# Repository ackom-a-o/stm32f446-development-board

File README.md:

# STM32F446 Development Board

A custom, USB-powered development board for sensor and control experiments, built around the **STM32F446ZET6**. This project follows an embedded hardware design from component selection and PCB layout through assembly preparation, firmware and bench validation.

**Current milestone: prototype fabrication preparation.** The corrected design, fabrication exports and assembly data are published below. Hardware is not yet bench-tested; final assembler production-file approval and physical validation remain open.

*Composed from the current fabrication Gerbers. Top copper and silkscreen only; drill holes are not depicted. This is a design view, not an assembled-board photograph.*

[Schematic PDF](docs/schematic.pdf) · [Engineering review](docs/engineering-review.md) · [Validation evidence](docs/validation.md) · [Manufacturing package](manufacturing/prototype-r3/) · [First power-up](docs/bring-up.md)

## What the board provides

| Area | Implementation |
|---|---|
| MCU | STM32F446ZET6, Arm Cortex-M4, LQFP-144 |
| PCB | 80 × 70 mm, four copper layers, nominal 1.6 mm |
| Power | USB 5 V → protection → TPS7A2533 regulator → TPS22918 load switch → 3.3 V |
| Connectivity | USB 2.0 full-speed device, SPI, I²C, UART, analog and GPIO headers |
| CAN expansion | Classical CAN 2.0B on J7: PD0/RX and PD1/TX; requires an external 3.3 V logic-compatible transceiver |
| Debug | External SWD probe through a custom five-pin header |
| Clock | 8 MHz crystal |
| User controls | Three pushbuttons and three indicator LEDs |

USB host operation, USB Power Delivery and motor-power delivery are outside the current scope. The load switch controls rail startup; it is not a programmable current limiter.

```mermaid
flowchart LR
    USB[USB-C 5 V] --> Protection[Fuse and series diode]
    Protection --> LDO[TPS7A2533 regulator]
    LDO --> Switch[TPS22918 load switch]
    Switch --> Rail[3.3 V MCU and headers]
    Host[USB host data] <--> ESD[USBLC6 protection]
    ESD <--> MCU[STM32F446]
    Probe[External SWD probe] <--> MCU
    MCU <--> IO[SPI / I2C / UART / GPIO]
    MCU <--> CANHeader[J7: PD0 RX / PD1 TX]
    CANHeader <--> Transceiver[External CAN transceiver - required]
    Transceiver <--> CANBus[CANH / CANL bus]
```

CAN uses the MCU's existing CAN1 controller through J7 pin 3 (PD0/CAN1_RX) and pin 4 (PD1/CAN1_TX), configured as AF9. The transceiver and bus termination are external to this PCB. This is Classical CAN, not CAN FD, and firmware/link testing is pending.

## Engineering work behind the layout

The layout was reviewed against MCU and power-component datasheets, ST's USB hardware guidance and published signal-integrity advice. Checks covered electrical connectivity, local bypassing, ground return paths, USB geometry, reset/crystal placement, sourcing, footprint fit and assembly orientation. The [engineering review](docs/engineering-review.md) records the reasoning, corrections, references and remaining limits.

- **Reset routing:** moving C22 reduced its MCU reset route from **19.45 mm to 13.41 mm**, about 31%. The [before/after comparison](docs/design-decisions.md#reset-layout-iteration) records the improvement and remaining compromise.
- **Power margin:** a **250 mA total design budget** was screened against regulator dropout and dissipation. It remains conditional until load and thermal measurements establish the board's operating envelope.
- **Local bypassing:** C29 adds a dedicated 1 µF capacitor at the TPS22918 input instead of relying only on the regulator's more distant output capacitor.
- **Ground return:** a short PG9 inner-layer crossing was moved to the top layer to restore local ground beneath SWDIO. Ground stitching was retained; a geometric screen found no missing reference samples along the checked outer-layer routes.
- **Routing corners:** the remaining ordinary PF6 right-angle bend was replaced with chamfered routing. The saved-board audit found zero ordinary track-to-track 90° bends within its stated scope. [Why prefer 45° bends?](docs/engineering-review.md#routing-corners-why-prefer-45-degrees) They reduce abrupt geometry changes; a right angle alone does not prove a signal will fail.
- **Assembly data:** the supplier preview exposed header and chip rotation mismatches. Corrections were put into the placement file, uploaded and checked after a full quote reload.

Peer feedback and AI-assisted checks supported these iterations. Bench measurements will be reported separately from calculations and software checks.

## Evidence and next milestone

Recorded checks on **22 October 2026** report **0 ERC issues, 0 DRC violations, 0 unconnected items and 0 schematic parity issues**, with no ignored checks or current exclusions. The published inventory contains **66 assembly references**, plus three PCB test points. [Validation evidence](docs/validation.md) links the source hashes, reports and geometric checks; these do not establish measured hardware performance.

The fabricator has confirmed the nominal **JLC04161H-7628** construction used as the design basis. Next: approve final production files and bring up the prototype. The [bring-up checklist](docs/bring-up.md) starts with inspection, shorts and power rails, then SWD/reset, clock startup, GPIO and USB. Every physical test in the [test log](docs/test-log.md) remains **not tested**. Firmware will be added when implementation begins.

## Explore the design

Open [`stm32.kicad_pro`](stm32.kicad_pro) in **KiCad 10**, with its standard libraries installed.

The [four-sheet schematic](docs/schematic.pdf) separates power, USB/debug/clock, peripheral interfaces and expansion. The MCU uses eight symbol units so that supply pins and GPIO ports can be reviewed separately. Named signals connect sheets; pin numbers retain their physical package mapping.

*Sheet 3 of 4. The earlier readability refactor preserved its then-current 68 physical references and all 135 nets; [historical comparison evidence](docs/checks/schematic-refactor.json) records unchanged PCB geometry for that refactor. The subsequent C29 addition brings the current physical-reference count to 69.*

| Files | Purpose |
|---|---|
| `stm32.kicad_sch` | Root sheet: power path and MCU supplies |
| `usb_debug_clock.kicad_sch` | USB, clock, reset, boot and SWD |
| `mcu_interfaces.kicad_sch`, `gpio_expansion.kicad_sch` | MCU ports, peripheral headers and expansion |
| `stm32.kicad_pcb` | Routed four-layer PCB |
| `stm32.kicad_dru` | Project design rules |
| `STM32_Custom.pretty`, `STM32_Power.kicad_sym`, `STM32_MCU.kicad_sym` | Local footprints, power symbols and split MCU symbol |
| `fp-lib-table`, `sym-lib-table` | Project-relative library configuration |
| `docs/` | Schematic export, design decisions, part inventory and validation evidence |

Local libraries are included. The empty `Library.pretty` directory is retained for the existing project library table. The [prototype-r3 package](manufacturing/prototype-r3/) contains Gerbers/drills, BOM, supplier-adjusted placement data and file hashes. It is an unvalidated prototype package, not a production-qualified release. Placement rotations are supplier-specific; another assembler must check its own conventions.

## References and licensing

[STM32F446 datasheet](https://www.st.com/resource/en/datasheet/stm32f446ze.pdf) · [TPS7A25 datasheet](https://www.ti.com/lit/ds/symlink/tps7a25.pdf) · [TPS22918 datasheet](https://www.ti.com/lit/ds/symlink/tps22918.pdf)

A project hardware/documentation license has not yet been selected. No explicit open-source license is currently granted. Third-party assets remain subject to their respective licenses.

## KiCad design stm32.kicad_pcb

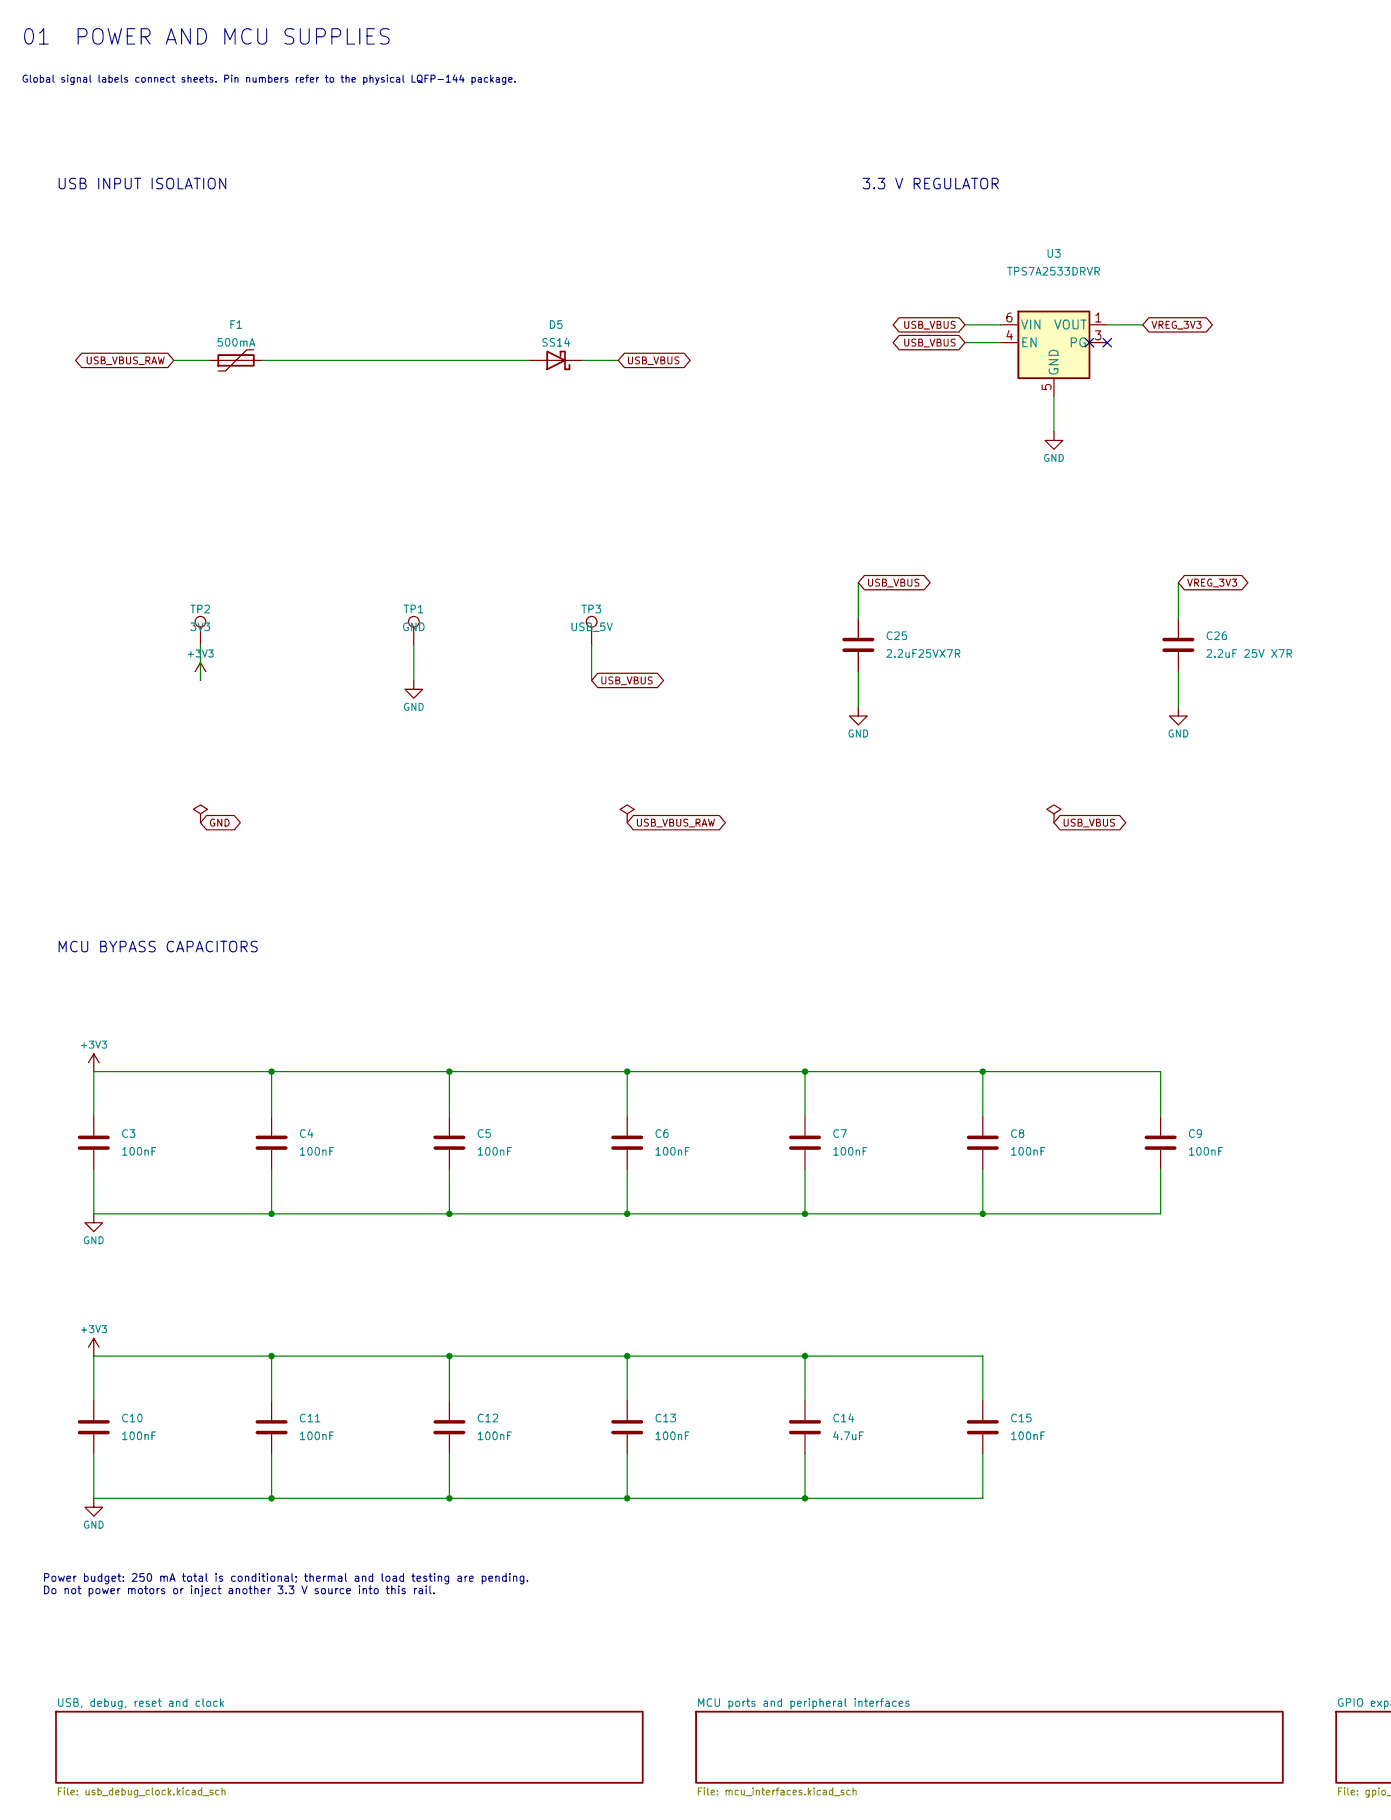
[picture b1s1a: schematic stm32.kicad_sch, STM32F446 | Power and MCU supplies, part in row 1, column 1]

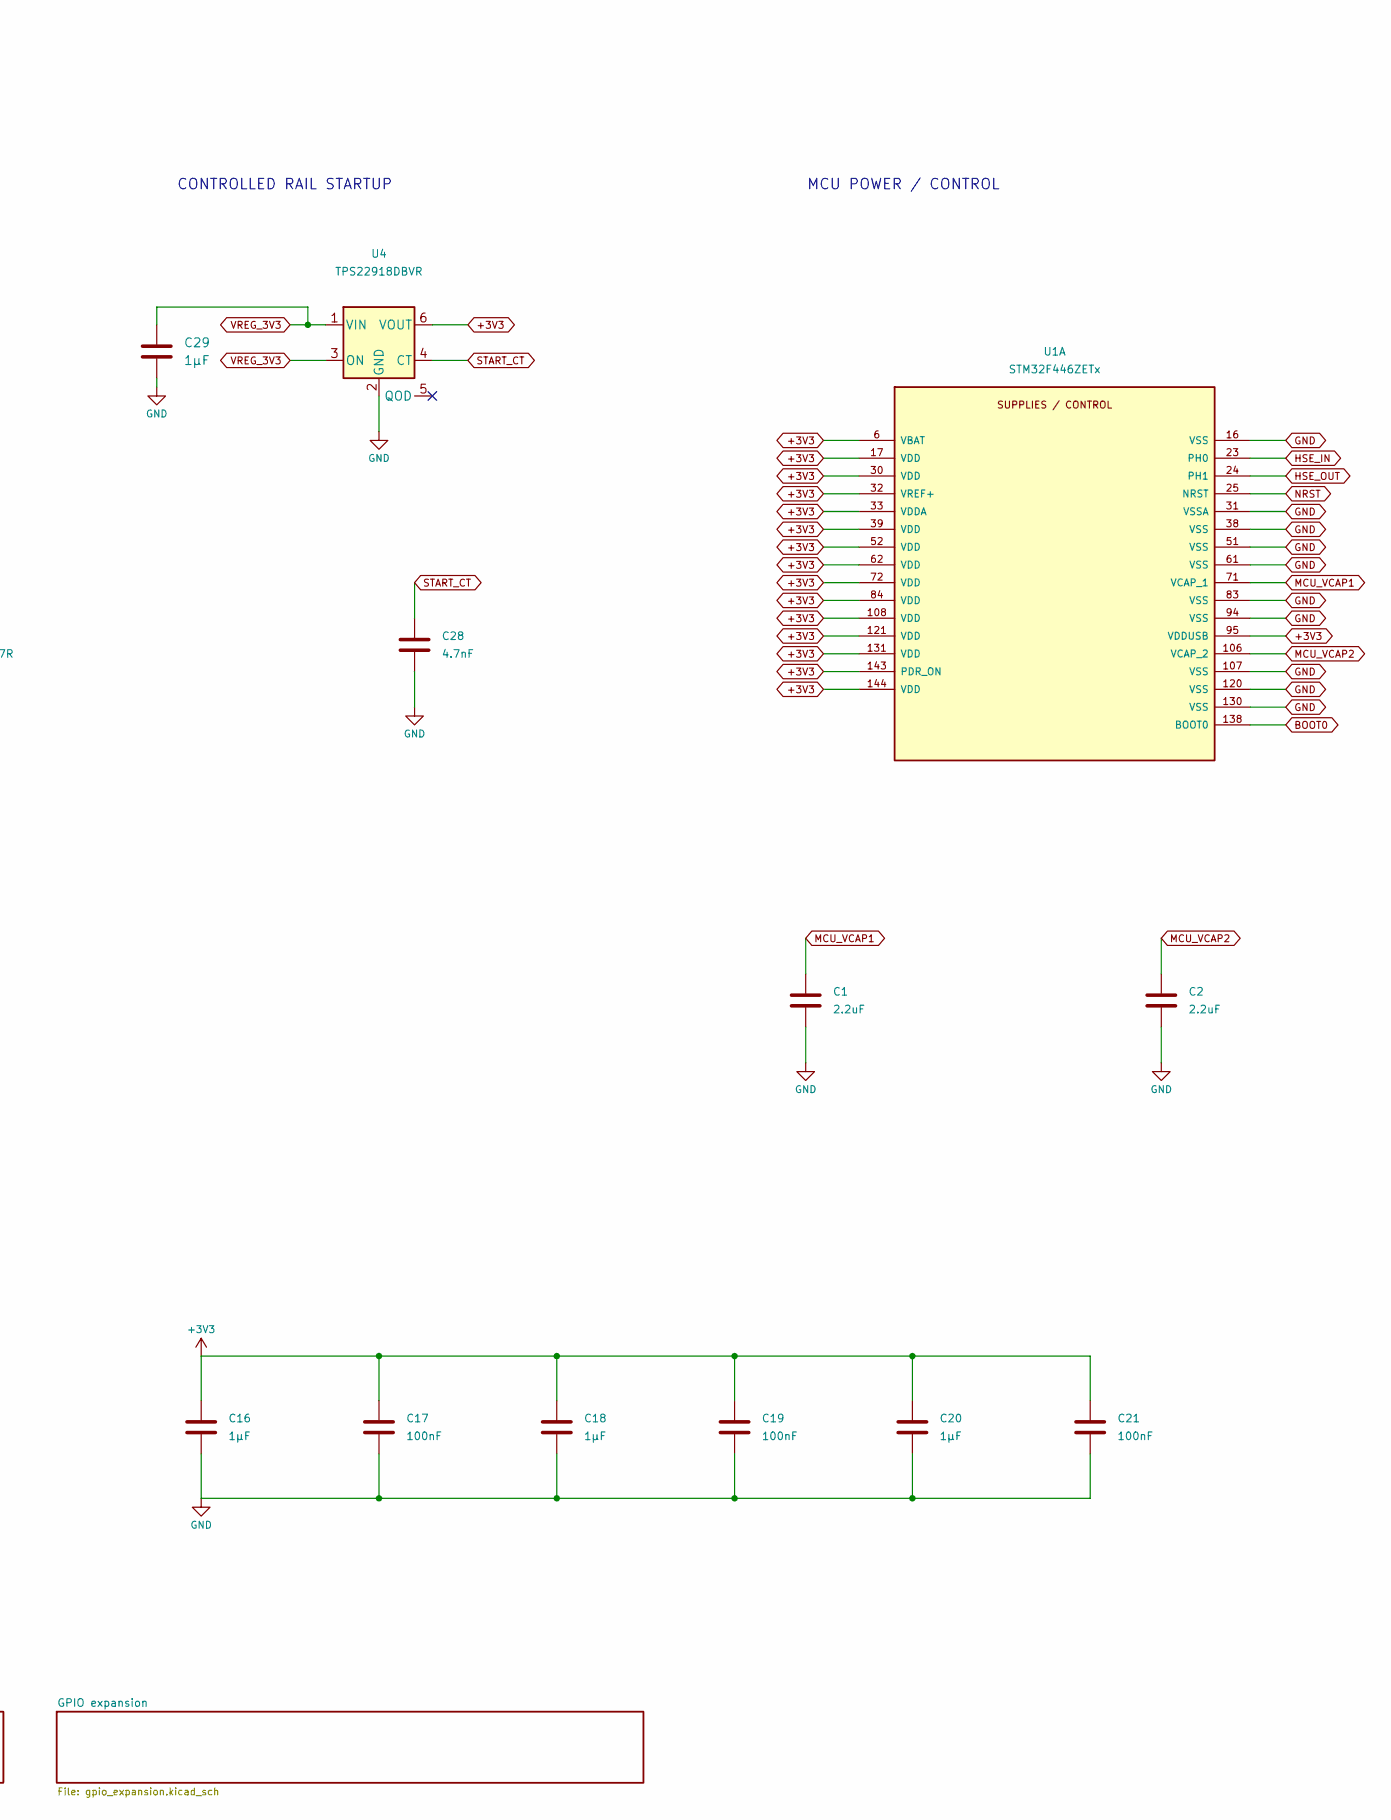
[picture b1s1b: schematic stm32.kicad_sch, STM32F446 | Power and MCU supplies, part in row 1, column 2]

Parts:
C1, C2: 2.2uF; C_0805_2012Metric; Manufacturer Part Number CL21B225KAFVPJE; LCSC Part Number C16195008
C3, C4, C5, C6, C7, C8, C9, C10, C11, C12, C13, C15, C17, C19, C21: 100nF; C_0805_2012Metric; Manufacturer Part Number CC0805KRX7R9BB104; LCSC Part Number C49678
C14: 4.7uF; C_0805_2012Metric; Manufacturer Part Number CL21A475KAQNNNE; LCSC Part Number C1779
C16, C18, C20: 1µF; C_0805_2012Metric; Manufacturer Part Number CL21B105KBFNNNE; LCSC Part Number C28323
C25: 2.2uF25VX7R; C_0805_2012Metric; Manufacturer Part Number CL21B225KAFVPJE; LCSC Part Number C16195008
C26: 2.2uF 25V X7R; C_0805_2012Metric; Manufacturer Part Number CL21B225KAFVPJE; LCSC Part Number C16195008
C28: 4.7nF; C_0805_2012Metric; Manufacturer Part Number CC0805KRX7R9BB472; LCSC Part Number C107153
C29: 1µF; C_0603_1608Metric; Manufacturer Part Number CL10B105KA8NNNC; LCSC Part Number C29936
D5: SS14; D_SMA; Manufacturer Part Number SS14; LCSC Part Number C2480
F1: 500mA; Fuse_1812_4532Metric; Manufacturer Part Number MF-MSMF050-2; LCSC Part Number C17313
TP1: GND; TestPoint_Pad_D2.0mm
TP2: 3V3; TestPoint_Pad_D2.0mm
TP3: USB_5V; TestPoint_Pad_D2.0mm
U1: STM32F446ZETx; LQFP-144_20x20mm_P0.5mm; Manufacturer Part Number STM32F446ZET6; LCSC Part Number C1337227
U3: TPS7A2533DRVR; TPS7A25_DRV0006A; Manufacturer Part Number TPS7A2533DRVR; LCSC Part Number C2867820
U4: TPS22918DBVR; TPS22918_DBV0006A; Manufacturer Part Number TPS22918DBVR; LCSC Part Number C131941

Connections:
+3V3: C3.1, C4.2, C5.1, C6.1, C7.1, C8.1, C9.2, C10.2, C11.2, C12.2, C13.2, C14.1, C15.1, C16.1, C17.2, C18.2, C19.1, C20.1, C21.2, TP2.1 (1_1), U1.6 (VBAT), U1.17 (VDD), U1.30 (VDD), U1.32 (VREF+), U1.33 (VDDA), U1.39 (VDD), U1.52 (VDD), U1.62 (VDD), U1.72 (VDD), U1.84 (VDD), U1.95 (VDDUSB), U1.108 (VDD), U1.121 (VDD), U1.131 (VDD), U1.143 (PDR_ON), U1.144 (VDD), U4.6 (VOUT); also elsewhere on the board
BOOT0: U1.138 (BOOT0); also elsewhere on the board
GND: C1.1, C2.2, C3.2, C4.1, C5.2, C6.2, C7.2, C8.2, C9.1, C10.1, C11.1, C12.1, C13.1, C14.2, C15.2, C16.2, C17.1, C18.1, C19.2, C20.2, C21.1, C25.2, C26.2, C28.2, C29.2, TP1.1 (1_1), U1.16 (VSS), U1.31 (VSSA), U1.38 (VSS), U1.51 (VSS), U1.61 (VSS), U1.83 (VSS), U1.94 (VSS), U1.107 (VSS), U1.120 (VSS), U1.130 (VSS), U3.5 (GND), U3.7 (EP), U4.2 (GND); also elsewhere on the board
HSE_IN: U1.23 (PH0); also elsewhere on the board
HSE_OUT: U1.24 (PH1); also elsewhere on the board
MCU_VCAP1: C1.2, U1.71 (VCAP_1)
MCU_VCAP2: C2.1, U1.106 (VCAP_2)
NRST: U1.25 (NRST); also elsewhere on the board
unnamed: D5.2 (A), F1.2
START_CT: C28.1, U4.4 (CT)
USB_VBUS: C25.1, D5.1 (K), TP3.1 (1_1), U3.4 (EN), U3.6 (VIN); also elsewhere on the board
USB_VBUS_RAW: F1.1; also elsewhere on the board
VREG_3V3: C26.1, C29.1, U3.1 (VOUT), U4.1 (VIN), U4.3 (ON)

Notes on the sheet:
USB INPUT ISOLATION
01 POWER AND MCU SUPPLIES
3.3 V REGULATOR
CONTROLLED RAIL STARTUP
Power budget: 250 mA total is conditional; thermal and load testing are pending. Do not power motors or inject another 3.3 V source into this rail.
MCU POWER / CONTROL
MCU BYPASS CAPACITORS
Global signal labels connect sheets. Pin numbers refer to the physical LQFP-144 package.

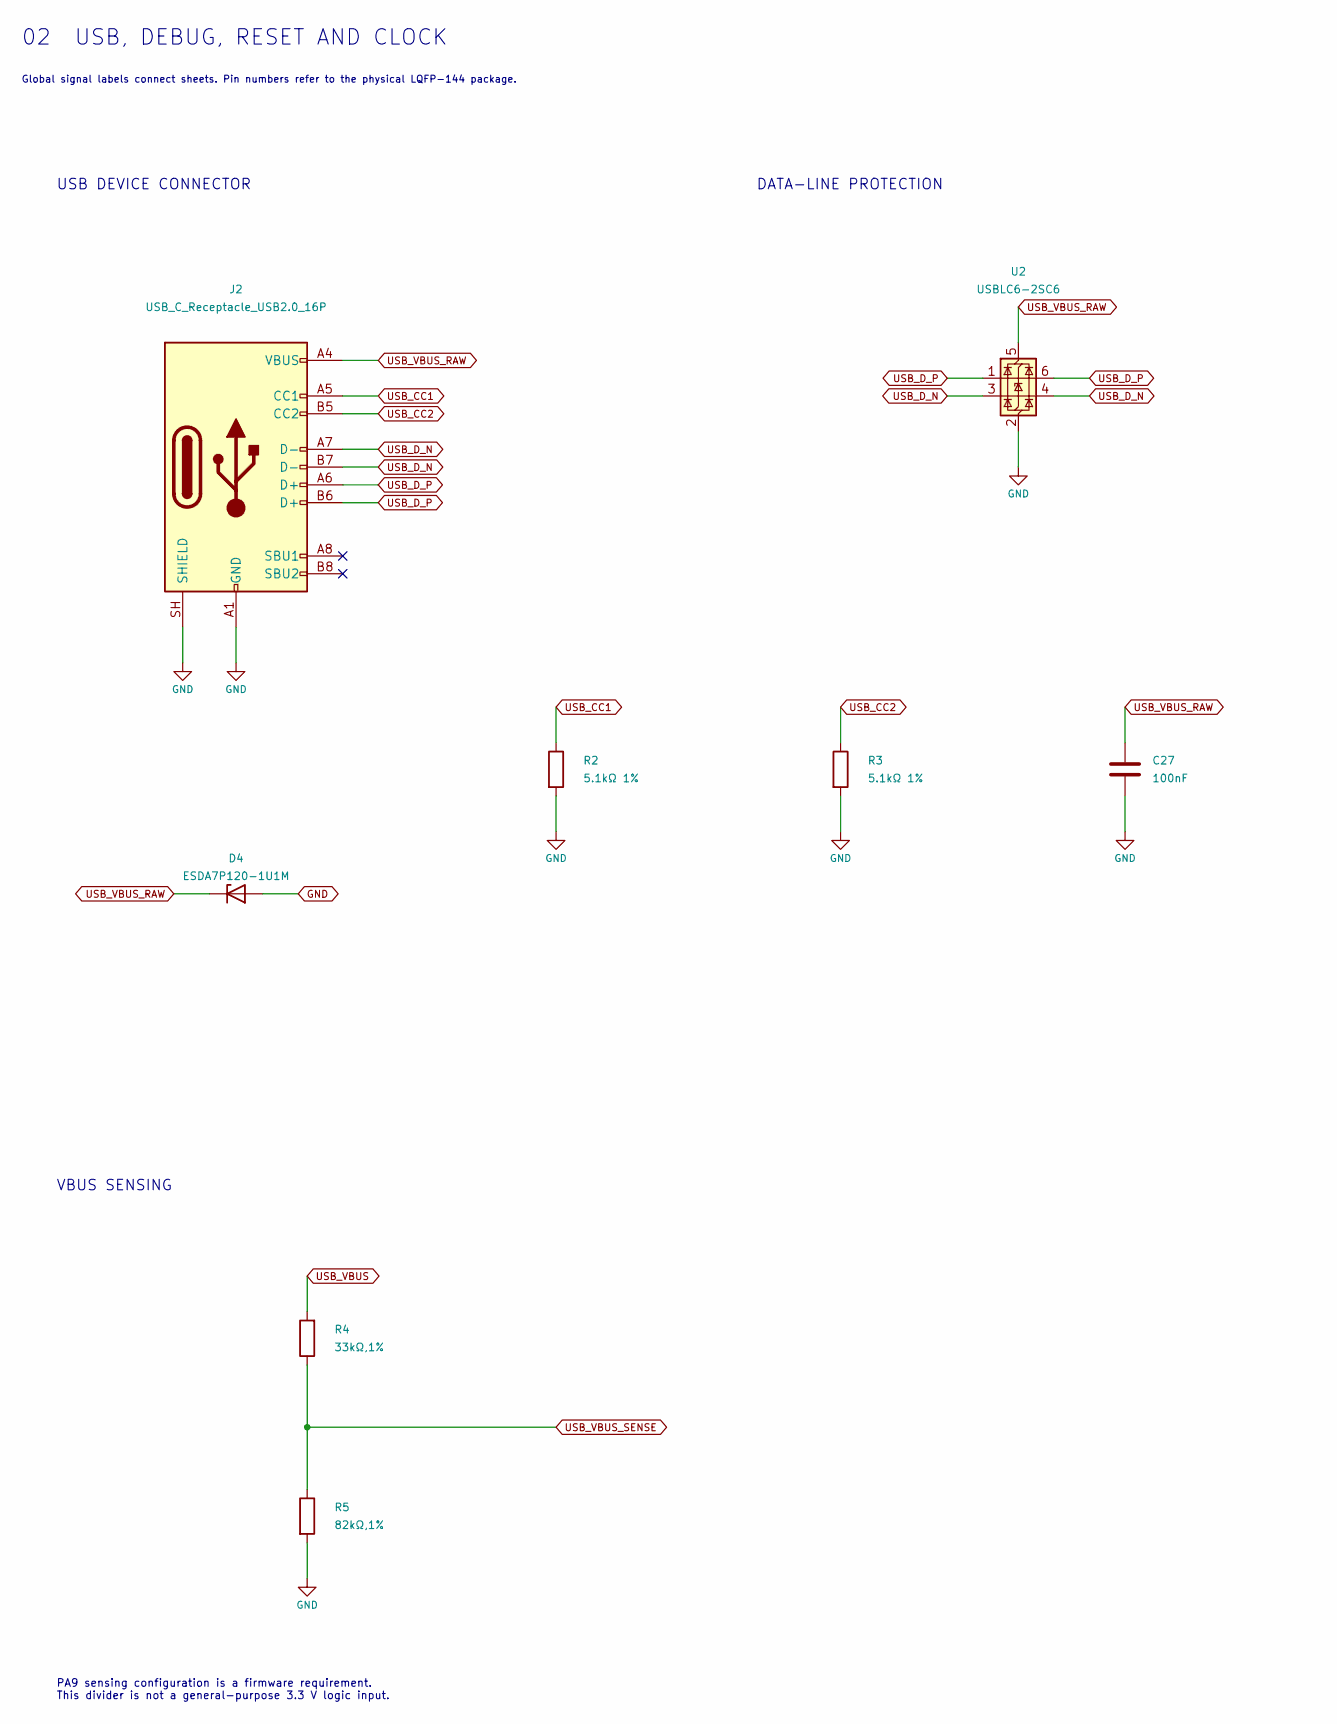
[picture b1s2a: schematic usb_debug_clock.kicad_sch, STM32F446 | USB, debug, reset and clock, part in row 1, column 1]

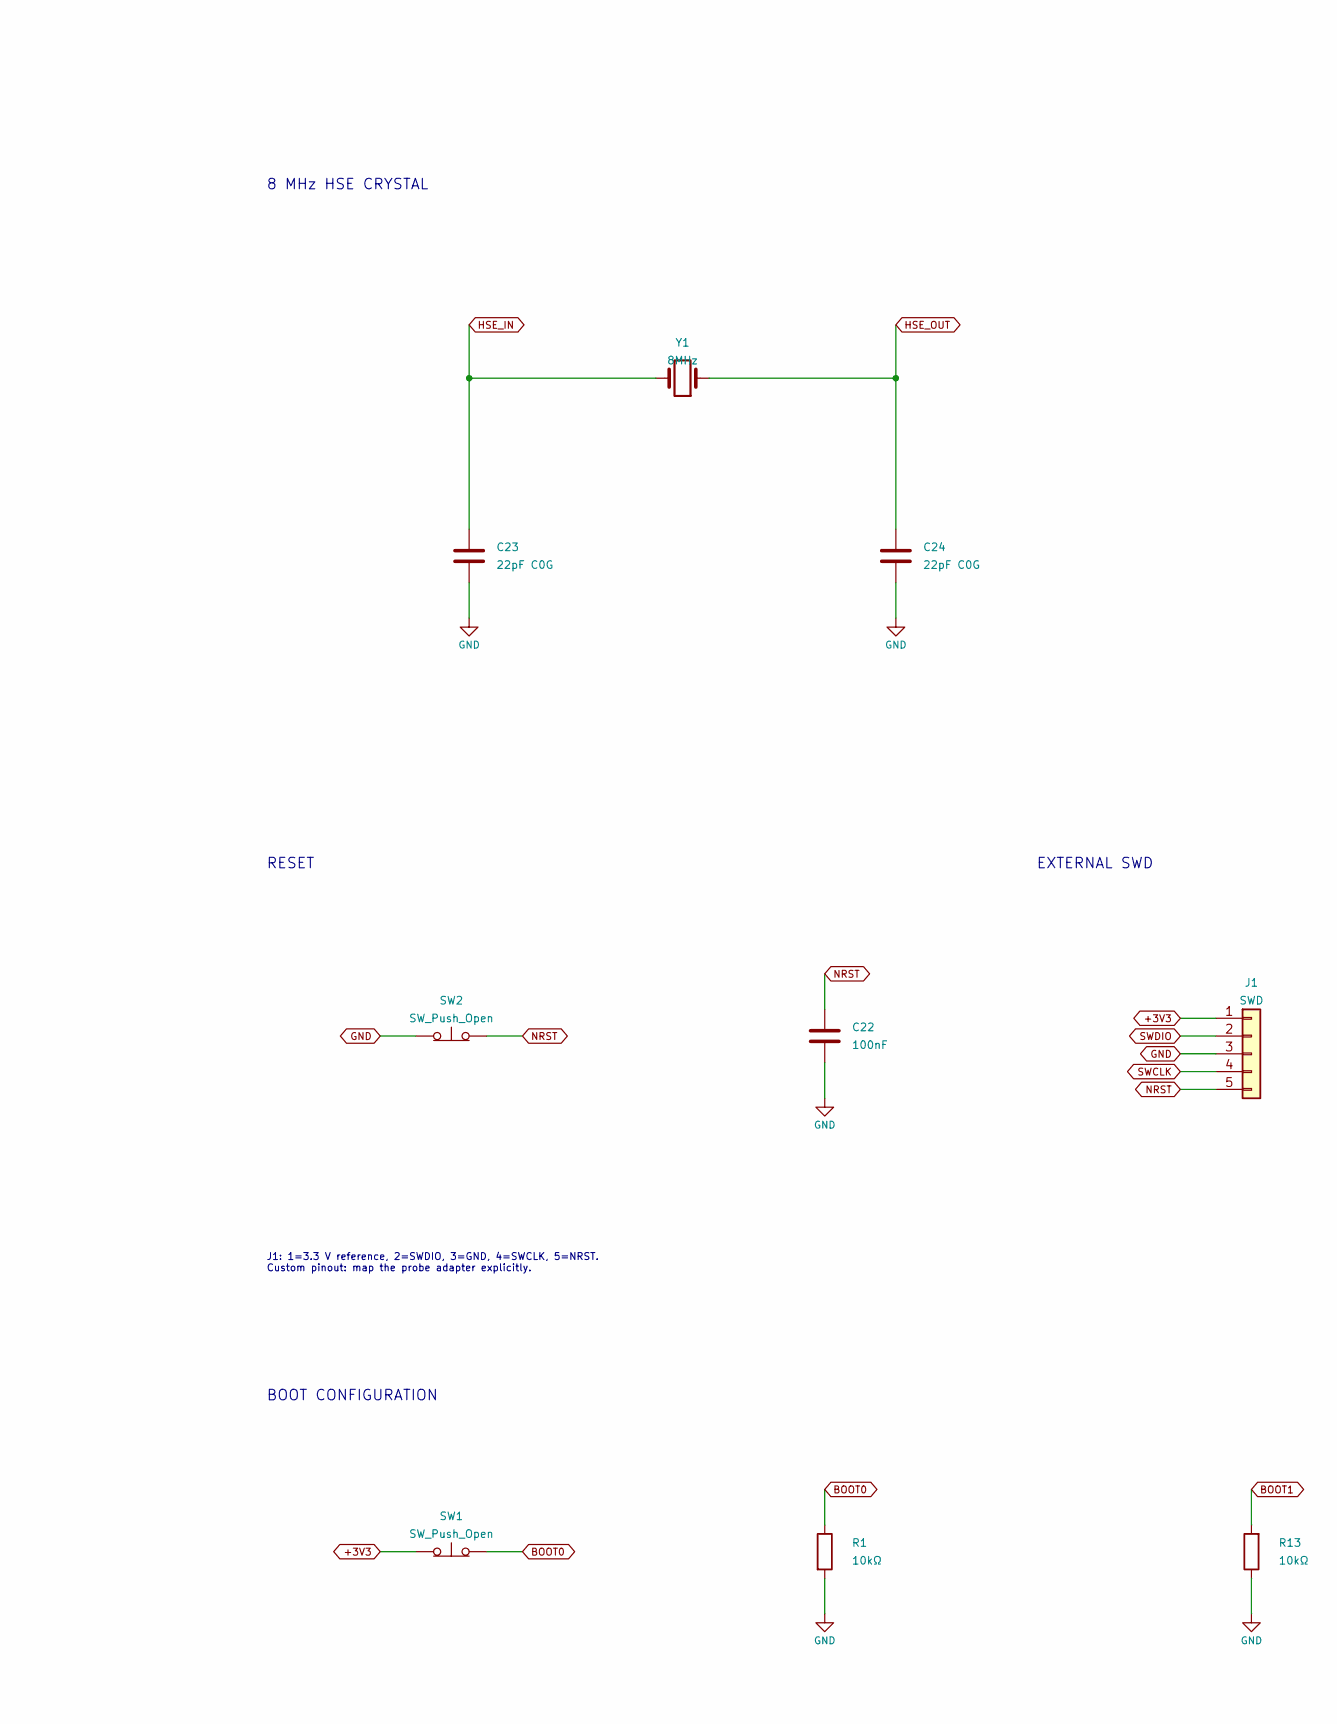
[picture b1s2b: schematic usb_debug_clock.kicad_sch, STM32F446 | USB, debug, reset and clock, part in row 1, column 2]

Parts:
C22, C27: 100nF; C_0805_2012Metric; Manufacturer Part Number CC0805KRX7R9BB104; LCSC Part Number C49678
C23, C24: 22pF C0G; C_0805_2012Metric; Manufacturer Part Number CL21C220JBANNNC; LCSC Part Number C1804
D4: ESDA7P120-1U1M; ESDA7P60-1U1M; Manufacturer Part Number ESDA7P120-1U1M; LCSC Part Number C2969802
J1: SWD; PinHeader_1x05_P2.54mm_Vertical; Manufacturer Part Number SH-PZ254V-1x5P; LCSC Part Number C55629812
J2: USB_C_Receptacle_USB2.0_16P; USB_C_Receptacle_USB4105_JLC; Manufacturer Part Number USB4105-GF-A-120; LCSC Part Number C5184243
R1, R13: 10kΩ; R_0805_2012Metric; Manufacturer Part Number 0805W8F1002T5E; LCSC Part Number C17414
R2, R3: 5.1kΩ 1%; R_0805_2012Metric; Manufacturer Part Number 0805W8F5101T5E; LCSC Part Number C27834
R4: 33kΩ,1%; R_0805_2012Metric; Manufacturer Part Number 0805W8F3302T5E; LCSC Part Number C17633
R5: 82kΩ,1%; R_0805_2012Metric; Manufacturer Part Number 0805W8F8202T5E; LCSC Part Number C17840
SW1, SW2: SW_Push_Open; SW_PUSH_6mm_H4.3mm; Manufacturer Part Number B3F-1000; LCSC Part Number C93157
U2: USBLC6-2SC6; SOT-23-6; Manufacturer Part Number USBLC6-2SC6; LCSC Part Number C7519
Y1: 8MHz; Crystal_SMD_Abracon_ABM3-2Pin_5.0x3.2mm; Manufacturer Part Number ECS-80-18-30-JGN-TR; LCSC Part Number C2450458

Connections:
+3V3: J1.1, SW1.1 (A); also elsewhere on the board
BOOT0: R1.1, SW1.2 (B); also elsewhere on the board
BOOT1: R13.2; also elsewhere on the board
GND: C22.1, C23.2, C24.2, C27.2, D4.2 (A), J1.3, J2.A1 (GND), J2.A12 (GND), J2.B1 (GND), J2.B12 (GND), J2.SH (SHIELD), R1.2, R2.2, R3.2, R5.2, R13.1, SW2.1 (A), U2.2 (GND); also elsewhere on the board
HSE_IN: C23.1, Y1.2; also elsewhere on the board
HSE_OUT: C24.1, Y1.1; also elsewhere on the board
NRST: C22.2, J1.5, SW2.2 (B); also elsewhere on the board
SWCLK: J1.4; also elsewhere on the board
SWDIO: J1.2; also elsewhere on the board
USB_CC1: J2.A5 (CC1), R2.1
USB_CC2: J2.B5 (CC2), R3.1
USB_D_N: J2.A7 (D-), J2.B7 (D-), U2.3 (I/O2), U2.4 (I/O2); also elsewhere on the board
USB_D_P: J2.A6 (D+), J2.B6 (D+), U2.1 (I/O1), U2.6 (I/O1); also elsewhere on the board
USB_VBUS: R4.2; also elsewhere on the board
USB_VBUS_RAW: C27.1, D4.1 (K), J2.A4 (VBUS), J2.A9 (VBUS), J2.B4 (VBUS), J2.B9 (VBUS), U2.5 (VBUS); also elsewhere on the board
USB_VBUS_SENSE: R4.1, R5.1; also elsewhere on the board

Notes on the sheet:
Global signal labels connect sheets. Pin numbers refer to the physical LQFP-144 package.
VBUS SENSING
8 MHz HSE CRYSTAL
EXTERNAL SWD
BOOT CONFIGURATION
USB DEVICE CONNECTOR
J1: 1=3.3 V reference, 2=SWDIO, 3=GND, 4=SWCLK, 5=NRST. Custom pinout: map the probe adapter explicitly.
RESET
02 USB, DEBUG, RESET AND CLOCK
PA9 sensing configuration is a firmware requirement. This divider is not a general-purpose 3.3 V logic input.
DATA-LINE PROTECTION

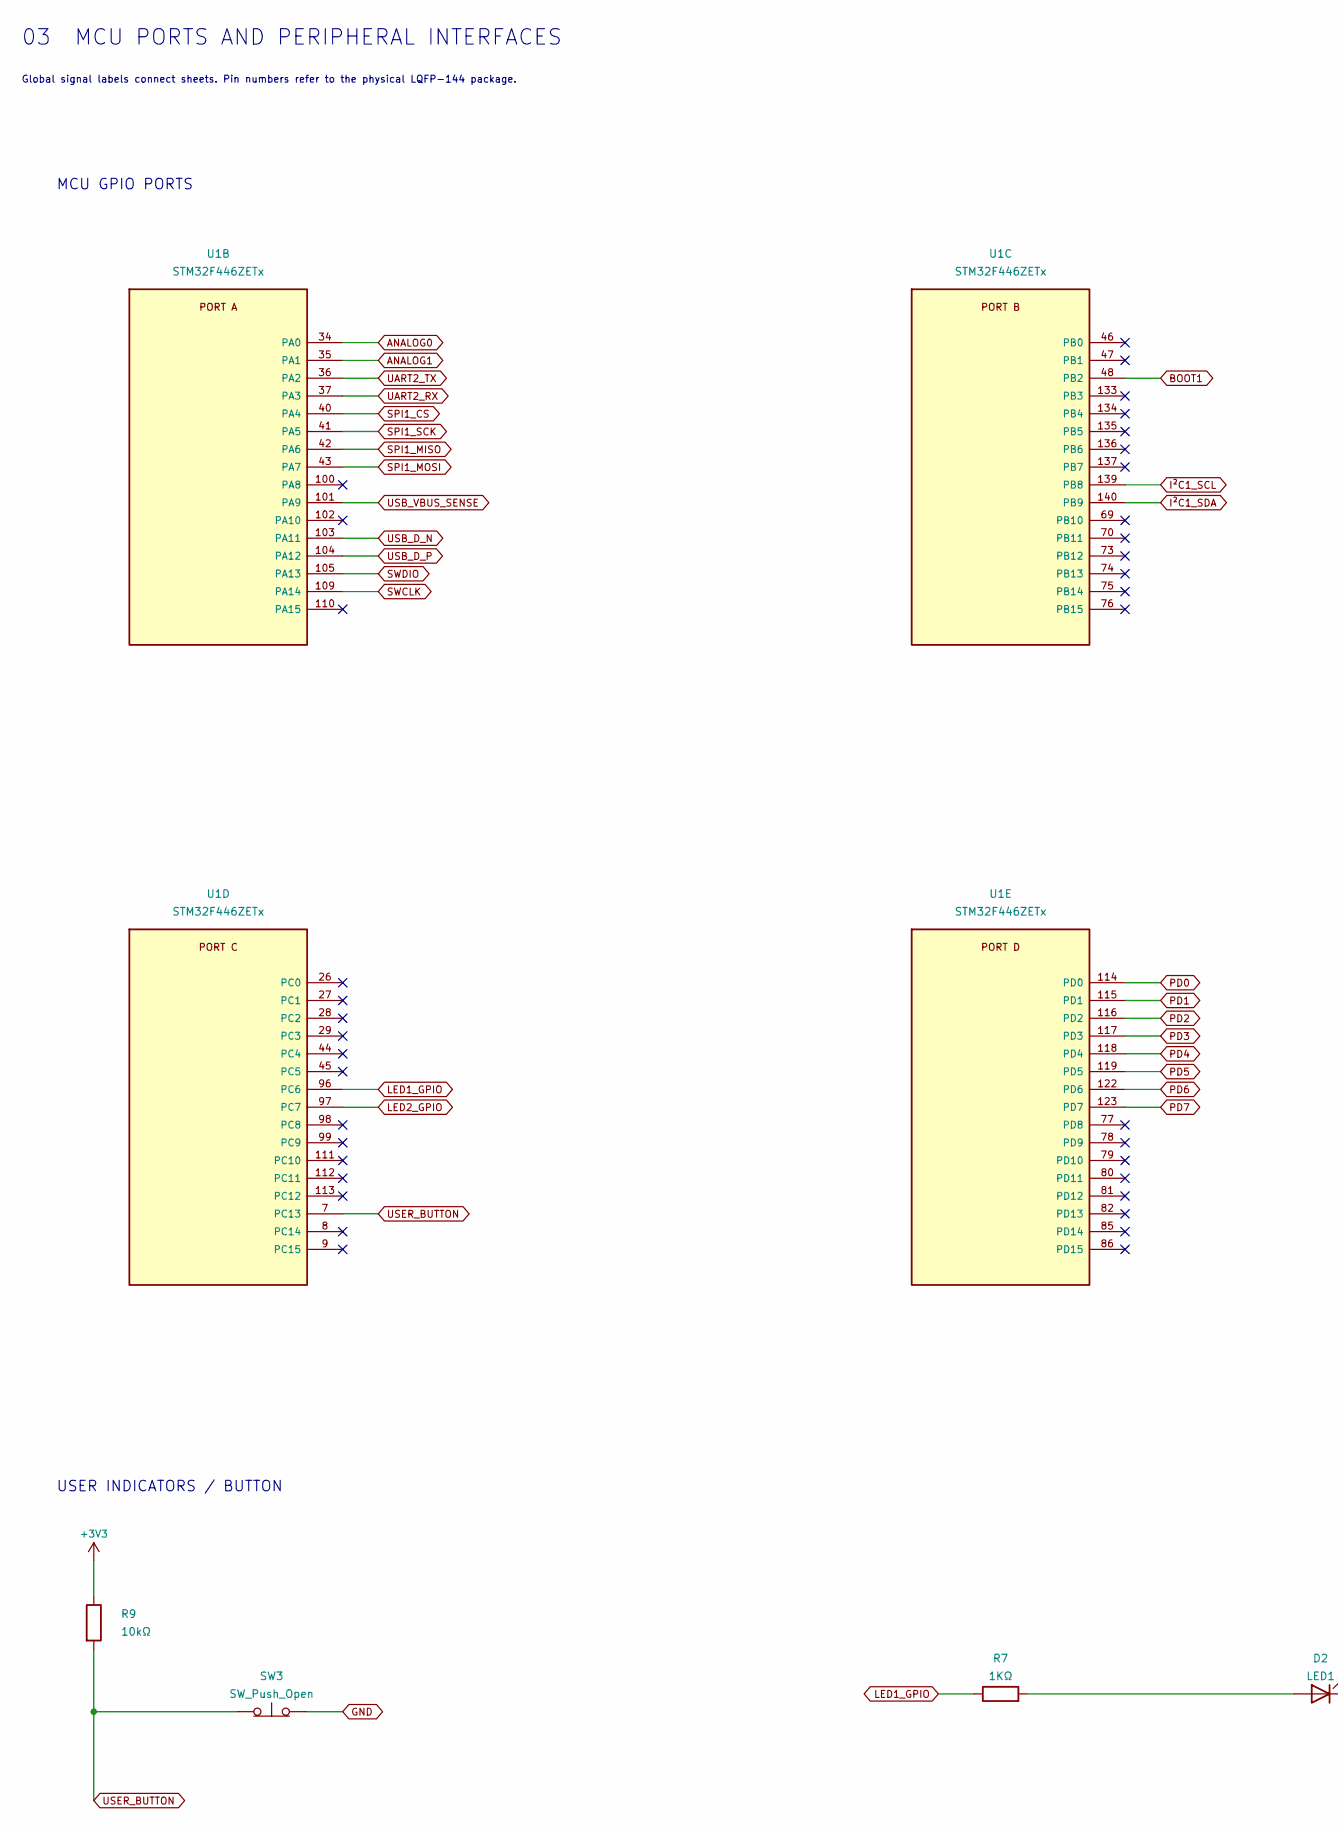
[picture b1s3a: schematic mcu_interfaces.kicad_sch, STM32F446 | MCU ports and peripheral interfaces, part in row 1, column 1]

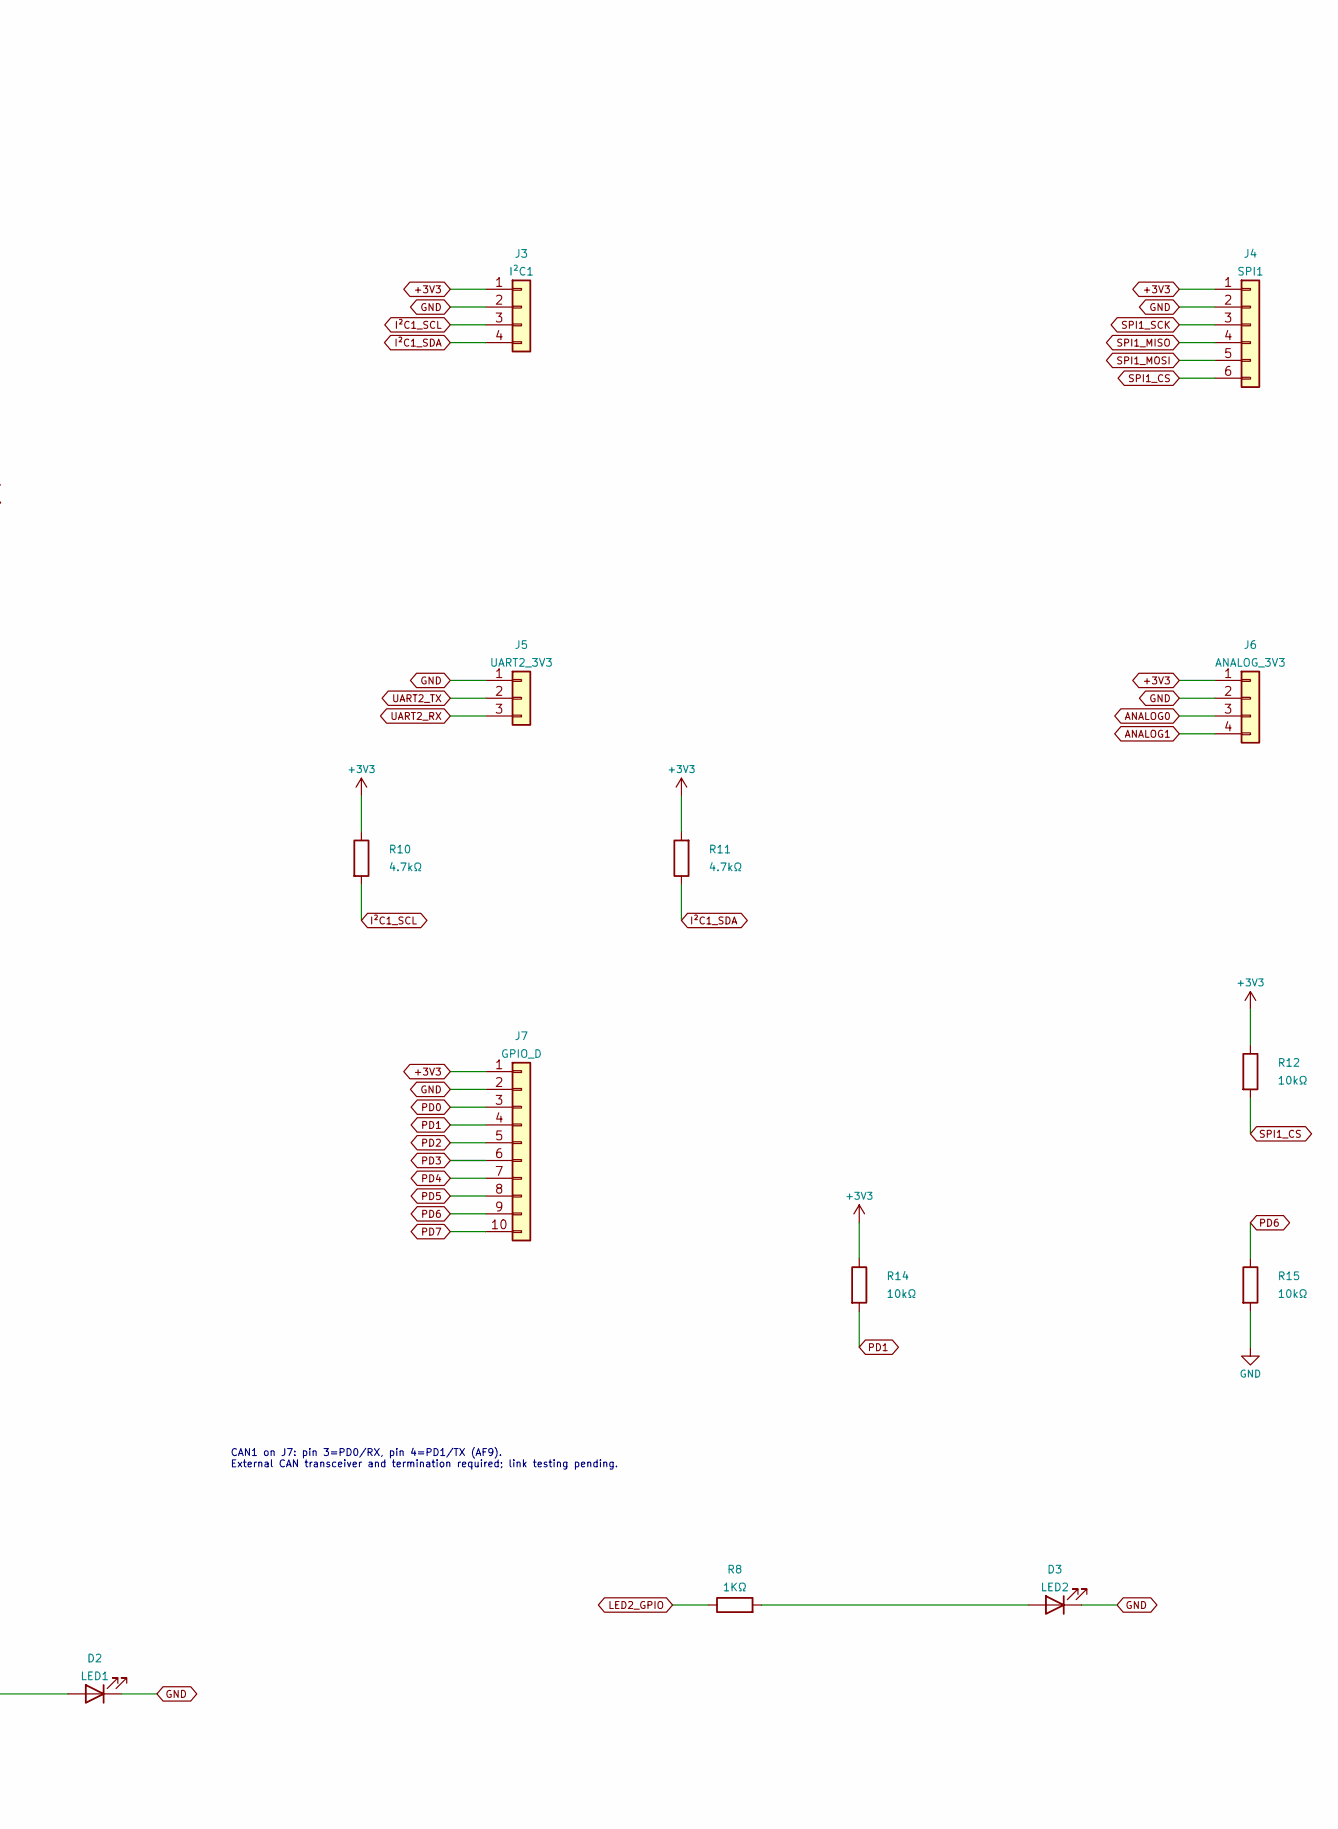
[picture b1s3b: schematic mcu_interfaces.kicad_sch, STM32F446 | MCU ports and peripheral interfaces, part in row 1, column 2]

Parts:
D2: LED1; LED_0805_2012Metric; Manufacturer Part Number KT-0805R; LCSC Part Number C2295
D3: LED2; LED_0805_2012Metric; Manufacturer Part Number KT-0805R; LCSC Part Number C2295
J3: I²C1; PinHeader_1x04_P2.54mm_Vertical; Manufacturer Part Number PZ254V-11-04P; LCSC Part Number C492403
J4: SPI1; PinHeader_1x06_P2.54mm_Vertical; Manufacturer Part Number CS-1109-1*6(L11.5); LCSC Part Number C5142852
J5: UART2_3V3; PinHeader_1x03_P2.54mm_Vertical; Manufacturer Part Number CS-1109-1X3(L11.5)PA6T; LCSC Part Number C18213718
J6: ANALOG_3V3; PinHeader_1x04_P2.54mm_Vertical; Manufacturer Part Number PZ254V-11-04P; LCSC Part Number C492403
J7: GPIO_D; PinHeader_1x10_P2.54mm_Vertical; Manufacturer Part Number PZ254V-11-10P; LCSC Part Number C492409
R7, R8: 1KΩ; R_0805_2012Metric; Manufacturer Part Number 0805W8F1001T5E; LCSC Part Number C17513
R9, R12, R14, R15: 10kΩ; R_0805_2012Metric; Manufacturer Part Number 0805W8F1002T5E; LCSC Part Number C17414
R10, R11: 4.7kΩ; R_0805_2012Metric; Manufacturer Part Number 0805W8F4701T5E; LCSC Part Number C17673
SW3: SW_Push_Open; SW_PUSH_6mm_H4.3mm; Manufacturer Part Number B3F-1000; LCSC Part Number C93157
U1: STM32F446ZETx; LQFP-144_20x20mm_P0.5mm; Manufacturer Part Number STM32F446ZET6; LCSC Part Number C1337227

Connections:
+3V3: J3.1, J4.1, J6.1, J7.1, R9.1, R10.1, R11.2, R12.1, R14.1; also elsewhere on the board
ANALOG0: J6.3, U1.34 (PA0)
ANALOG1: J6.4, U1.35 (PA1)
BOOT1: U1.48 (PB2); also elsewhere on the board
GND: D2.1 (K), D3.1 (K), J3.2, J4.2, J5.1, J6.2, J7.2, R15.2, SW3.2 (B); also elsewhere on the board
I²C1_SCL: J3.3, R10.2, U1.139 (PB8)
I²C1_SDA: J3.4, R11.1, U1.140 (PB9)
LED1_GPIO: R7.1, U1.96 (PC6)
LED2_GPIO: R8.1, U1.97 (PC7)
unnamed: D2.2 (A), R7.2
unnamed: D3.2 (A), R8.2
PD0: J7.3, U1.114 (PD0)
PD1: J7.4, R14.2, U1.115 (PD1)
PD2: J7.5, U1.116 (PD2)
PD3: J7.6, U1.117 (PD3)
PD4: J7.7, U1.118 (PD4)
PD5: J7.8, U1.119 (PD5)
PD6: J7.9, R15.1, U1.122 (PD6)
PD7: J7.10, U1.123 (PD7)
SPI1_CS: J4.6, R12.2, U1.40 (PA4)
SPI1_MISO: J4.4, U1.42 (PA6)
SPI1_MOSI: J4.5, U1.43 (PA7)
SPI1_SCK: J4.3, U1.41 (PA5)
SWCLK: U1.109 (PA14); also elsewhere on the board
SWDIO: U1.105 (PA13); also elsewhere on the board
UART2_RX: J5.3, U1.37 (PA3)
UART2_TX: J5.2, U1.36 (PA2)
USB_D_N: U1.103 (PA11); also elsewhere on the board
USB_D_P: U1.104 (PA12); also elsewhere on the board
USB_VBUS_SENSE: U1.101 (PA9); also elsewhere on the board
USER_BUTTON: R9.2, SW3.1 (A), U1.7 (PC13)

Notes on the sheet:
USER INDICATORS / BUTTON
CAN1 on J7: pin 3=PD0/RX, pin 4=PD1/TX (AF9). External CAN transceiver and termination required; link testing pending.
Global signal labels connect sheets. Pin numbers refer to the physical LQFP-144 package.
MCU GPIO PORTS
03 MCU PORTS AND PERIPHERAL INTERFACES
